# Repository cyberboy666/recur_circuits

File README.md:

# recur_circuits (archived)
was a collection of extension circuits for [r_e_c_u_r](https://github.com/cyberboy666/r_e_c_u_r) video sampler

these projects have been moved to their own repos:

- [i_n_c_u_r](https://github.com/cyberboy666/i_n_c_u_r) - adding knobs, cv and serial midi control
- [c_l_i_k_r](https://github.com/cyberboy666/c_l_i_k_r) - custom keypad/midi controller
- NEO_RECUR - still a WIP; watch this space

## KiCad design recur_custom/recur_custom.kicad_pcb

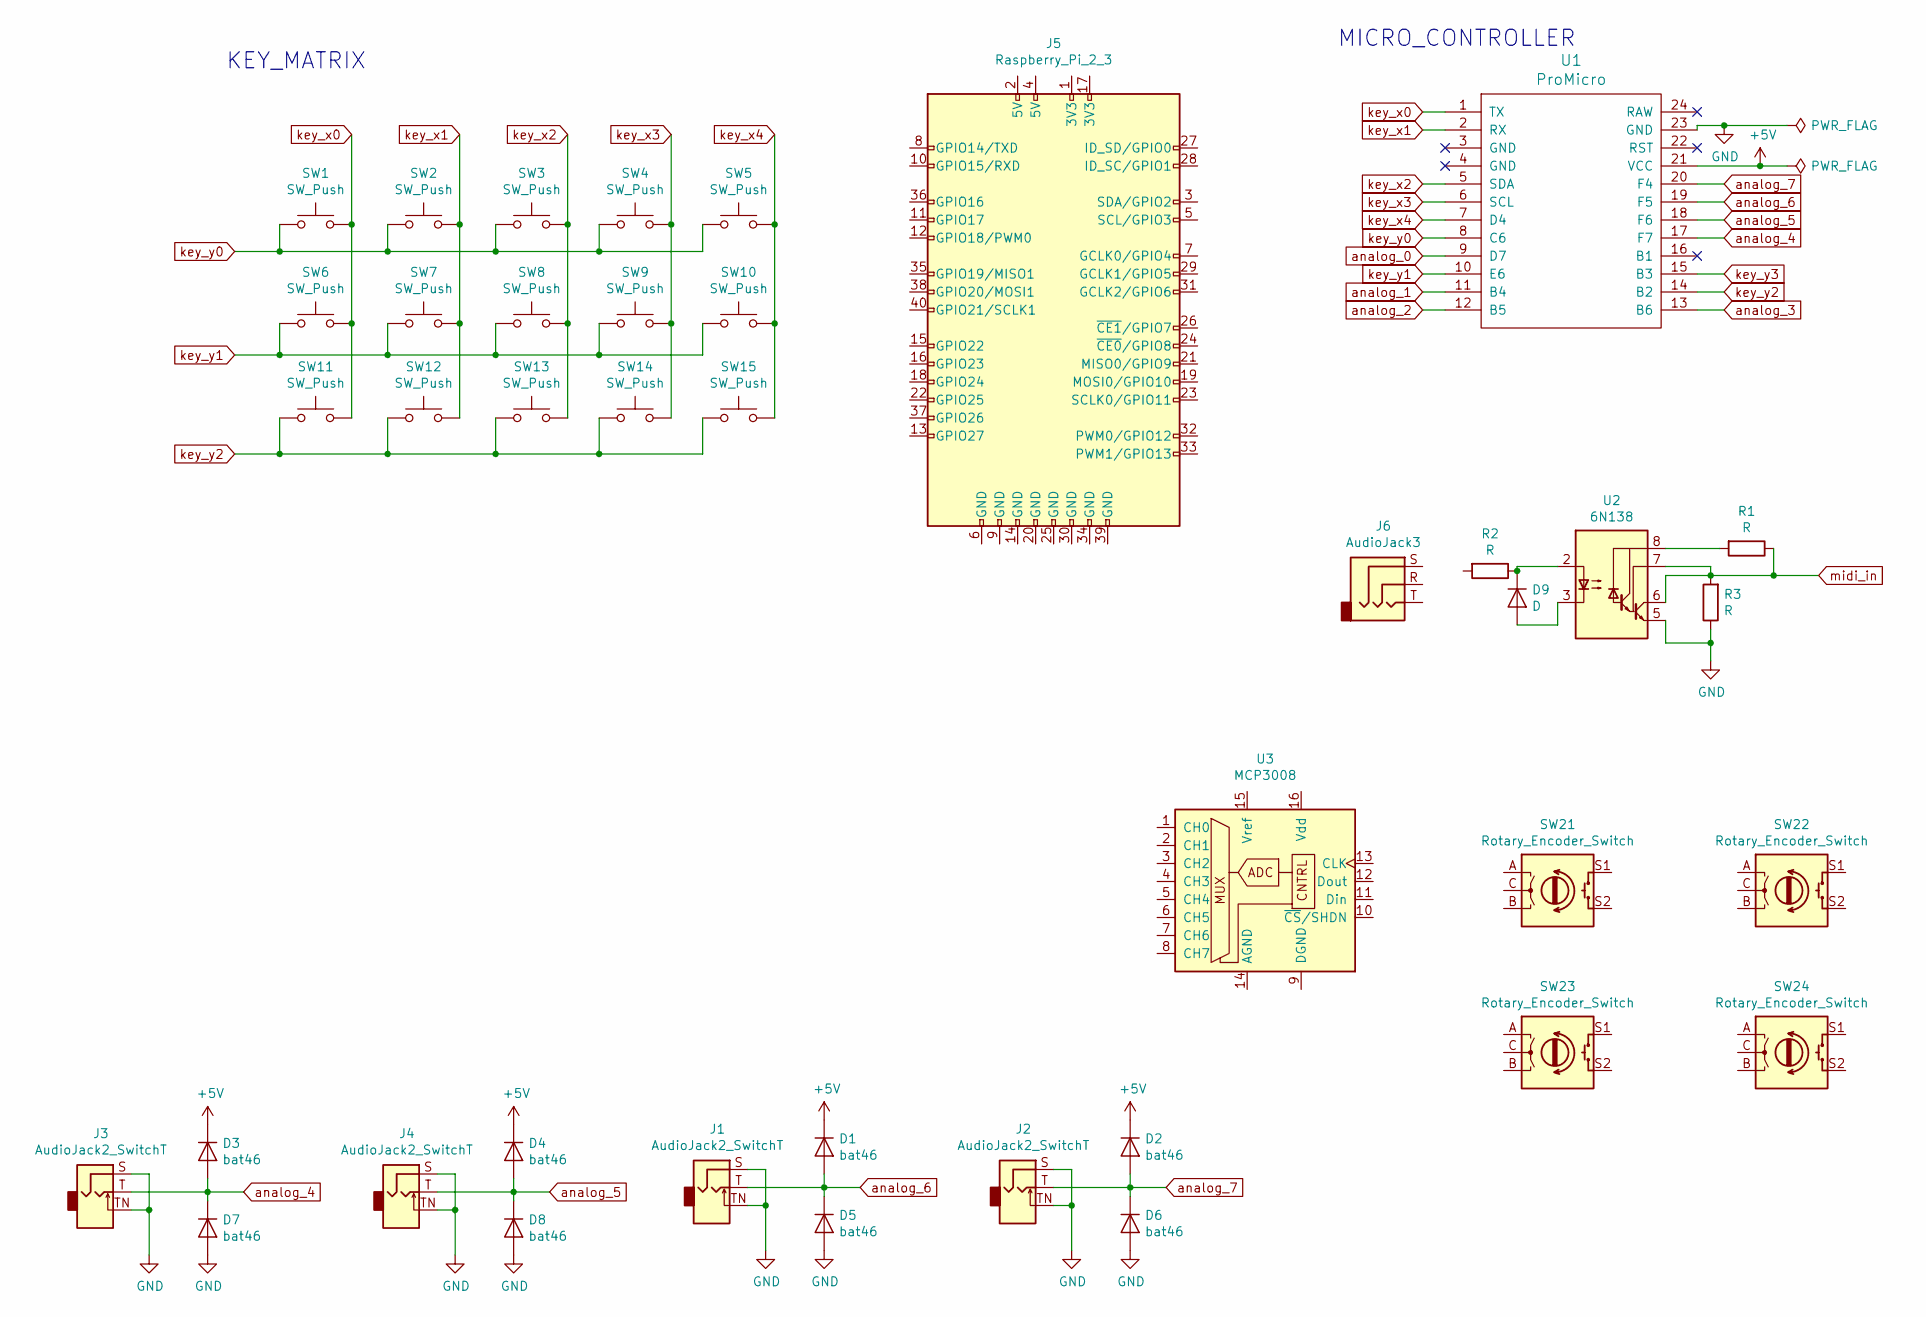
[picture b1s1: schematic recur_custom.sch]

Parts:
D1, D2, D3, D4, D5, D6, D7, D8: bat46; D_DO-34_SOD68_P7.62mm_Horizontal
D9: D; D_DO-34_SOD68_P7.62mm_Horizontal
J1, J2, J3, J4: AudioJack2_SwitchT; Tayda_3.5mm_stereo_TRS_jack_A-853
J5: Raspberry_Pi_2_3; MODULE_RASPBERRYPI4_4GB
J6: AudioJack3; Tayda_3.5mm_stereo_TRS_jack_A-853
R1, R2, R3: R; R_Axial_DIN0207_L6.3mm_D2.5mm_P5.08mm_Vertical
SW1, SW2, SW3, SW4, SW5, SW6, SW7, SW8, SW9, SW10, SW11: SW_Push; SW_Cherry_MX_1.00u_PCB
SW12, SW13, SW14, SW15: SW_Push; SW_PUSH_6mm_H7.3mm
SW21, SW22, SW23, SW24: Rotary_Encoder_Switch; RotaryEncoder_Alps_EC11E-Switch_Vertical_H20mm_CircularMoun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
U1: ProMicro
U2: 6N138; DIP-8-16_W7.62mm
U3: MCP3008; DIP-16_W7.62mm

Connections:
+5V: D1.1 (K), D2.1 (K), D3.1 (K), D4.1 (K), U1.21 (VCC)
GND: D5.2 (A), D6.2 (A), D7.2 (A), D8.2 (A), J1.S, J1.TN, J2.S, J2.TN, J3.S, J3.TN, J4.S, J4.TN, R3.1, U1.23 (GND), U2.5 (GND)
unnamed: D9.1 (K), R2.1, U2.2 (C1)
unnamed: D9.2 (A), U2.3 (C2)
unnamed: R1.2, U2.8 (VCC)
analog_0: U1.9 (D7)
analog_1: U1.11 (B4)
analog_2: U1.12 (B5)
analog_3: U1.13 (B6)
analog_4: D3.2 (A), D7.1 (K), J3.T, U1.17 (F7)
analog_5: D4.2 (A), D8.1 (K), J4.T, U1.18 (F6)
analog_6: D1.2 (A), D5.1 (K), J1.T, U1.19 (F5)
analog_7: D2.2 (A), D6.1 (K), J2.T, U1.20 (F4)
key_x0: SW1.2, SW6.2, SW11.2, U1.1 (TX); also elsewhere on the board
key_x1: SW2.2, SW7.2, SW12.2, U1.2 (RX)
key_x2: SW3.2, SW8.2, SW13.2, U1.5 (SDA)
key_x3: SW4.2, SW9.2, SW14.2, U1.6 (SCL); also elsewhere on the board
key_x4: SW5.2, SW10.2, SW15.2, U1.7 (D4)
key_y0: SW1.1, SW2.1, SW3.1, SW4.1, SW5.1, U1.8 (C6)
key_y1: SW6.1, SW7.1, SW8.1, SW9.1, SW10.1, U1.10 (E6)
key_y2: SW11.1, SW12.1, SW13.1, SW14.1, SW15.1, U1.14 (B2)
key_y3: U1.15 (B3); also elsewhere on the board
midi_in: R1.1, R3.2, U2.6 (VO2), U2.7 (VO1)

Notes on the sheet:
KEY_MATRIX
MICRO_CONTROLLER

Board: 2 copper layers, 40 parts (0 on the bottom side), 17 nets, no tracks yet.

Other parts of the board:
SW16, SW19: SW_Push; SW_Cherry_MX_1.00u_PCB

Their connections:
key_x0: SW16.2; also elsewhere on the board
key_x3: SW19.2; also elsewhere on the board
key_y3: SW16.1, SW19.1; also elsewhere on the board

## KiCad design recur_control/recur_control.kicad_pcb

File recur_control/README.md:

# recur control circuit

this is a lil circuit that aims to offer a low-cost alternative to using cheapo plastic numpads to control recur. when i first designed recur i decided to use [these](https://www.aliexpress.com/item/4000748567192.html) numpads from aliexpress. my main goals at the time were making the project as simple and accessable as possible. however over the last few years many people have had problems using (possible variations?) of these numpads and others. seemingly similar devices run conflicting firmware, different layout of keys on different versions, crashes, gross hacks needed in the code, partial working units, and many more frustrating problems that are impossible for me to debug without owning every differnet device. i am also aware of contributing to the consumption of ecologically and ethically problematic products by endorsing these devices..

alsonow that recur has evolved beyond just a sample-player, having continuous control over parameters (like shaders) is more important than it was before. still one of the best options is to use a korg-nano-kontrol or similar midi controller as this gives many faders to control effects with. however for people who dont have a nanokontrol or want to use it elsewhere in their setup, i have been thinking of a small cheap and simple alterative to using numpads:

- 20x tac-switches for discrete control
- (optional) 4x pot + 4x cv for continuous control
- firmware can be set to act as midi device (required for cc ) or keyboard device
- shouldnt come to much more than 10€ cost in parts (ofcourse more for kits/assembled if i ever get round to this)

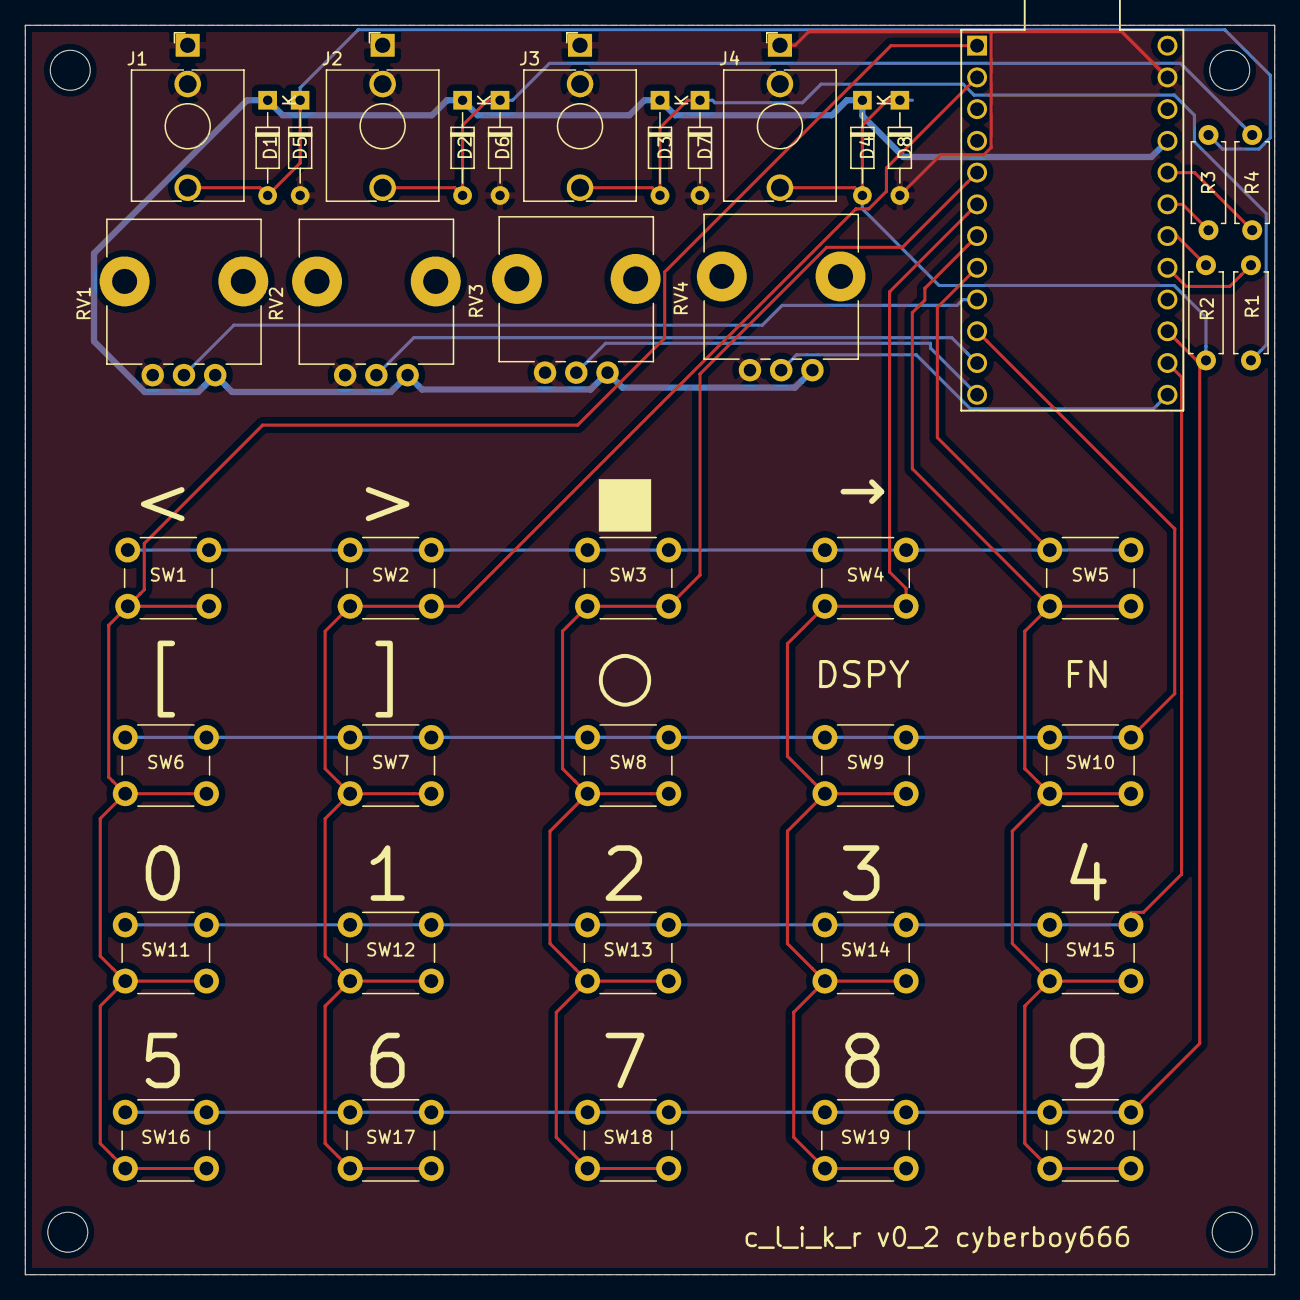
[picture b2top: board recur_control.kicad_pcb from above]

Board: 2 copper layers, 100.0 x 100.0 mm, 41 parts (0 on the bottom side), 23 nets.

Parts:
D1, D2, D3, D4, D5, D6, D7, D8: bat46; D_DO-34_SOD68_P7.62mm_Horizontal
J1, J2, J3, J4: mono_jack_3.5mm; Jack_3.5mm_QingPu_WQP-PJ398SM_Vertical_CircularHoles
R1, R2, R3, R4: 1k; R_Axial_DIN0207_L6.3mm_D2.5mm_P7.62mm_Horizontal
RV1, RV2, RV3, RV4: 10k_pot; Potentiometer_Alps_RK09L_Single_Vertical
SW1, SW2, SW3, SW4, SW5, SW6, SW7, SW8, SW9, SW10, SW11, SW12, SW13, SW14, SW15, SW16, SW17, SW18, SW19, SW20: Push; SW_PUSH_6mm_H7.3mm
U1: ProMicro

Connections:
+5V: D1.1, D2.1, D3.1, D4.1, RV1.1, RV2.1, RV3.1, RV4.1, U1.21
GND: D5.2, D6.2, D7.2, D8.2, J1.S, J1.TN, J2.S, J2.TN, J3.S, J3.TN, J4.S, J4.TN, RV1.3, RV2.3, RV3.3, RV4.3, U1.23
unnamed: D1.2, D5.1, J1.T, R3.2
unnamed: D2.2, D6.1, J2.T, R4.2
unnamed: D3.2, D7.1, J3.T, R1.2
unnamed: D4.2, D8.1, J4.T, R2.2
analog_0: RV1.2, U1.9
analog_1: RV2.2, U1.11
analog_2: RV3.2, U1.12
analog_3: RV4.2, U1.13
analog_4: R1.1, U1.17
analog_5: R2.1, U1.18
analog_6: R3.1, U1.19
analog_7: R4.1, U1.20
key_x0: SW1.2, SW6.2, SW11.2, SW16.2, U1.1
key_x1: SW2.2, SW7.2, SW12.2, SW17.2, U1.2
key_x2: SW3.2, SW8.2, SW13.2, SW18.2, U1.5
key_x3: SW4.2, SW9.2, SW14.2, SW19.2, U1.6
key_x4: SW5.2, SW10.2, SW15.2, SW20.2, U1.7
key_y0: SW1.1, SW2.1, SW3.1, SW4.1, SW5.1, U1.8
key_y1: SW6.1, SW7.1, SW8.1, SW9.1, SW10.1, U1.10
key_y2: SW11.1, SW12.1, SW13.1, SW14.1, SW15.1, U1.14
key_y3: SW16.1, SW17.1, SW18.1, SW19.1, SW20.1, U1.15

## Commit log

2020-10-21 add recur control circuit
2021-07-14 clikr circuit revision and start of code
2022-01-11 add brainstorm for new recur design
